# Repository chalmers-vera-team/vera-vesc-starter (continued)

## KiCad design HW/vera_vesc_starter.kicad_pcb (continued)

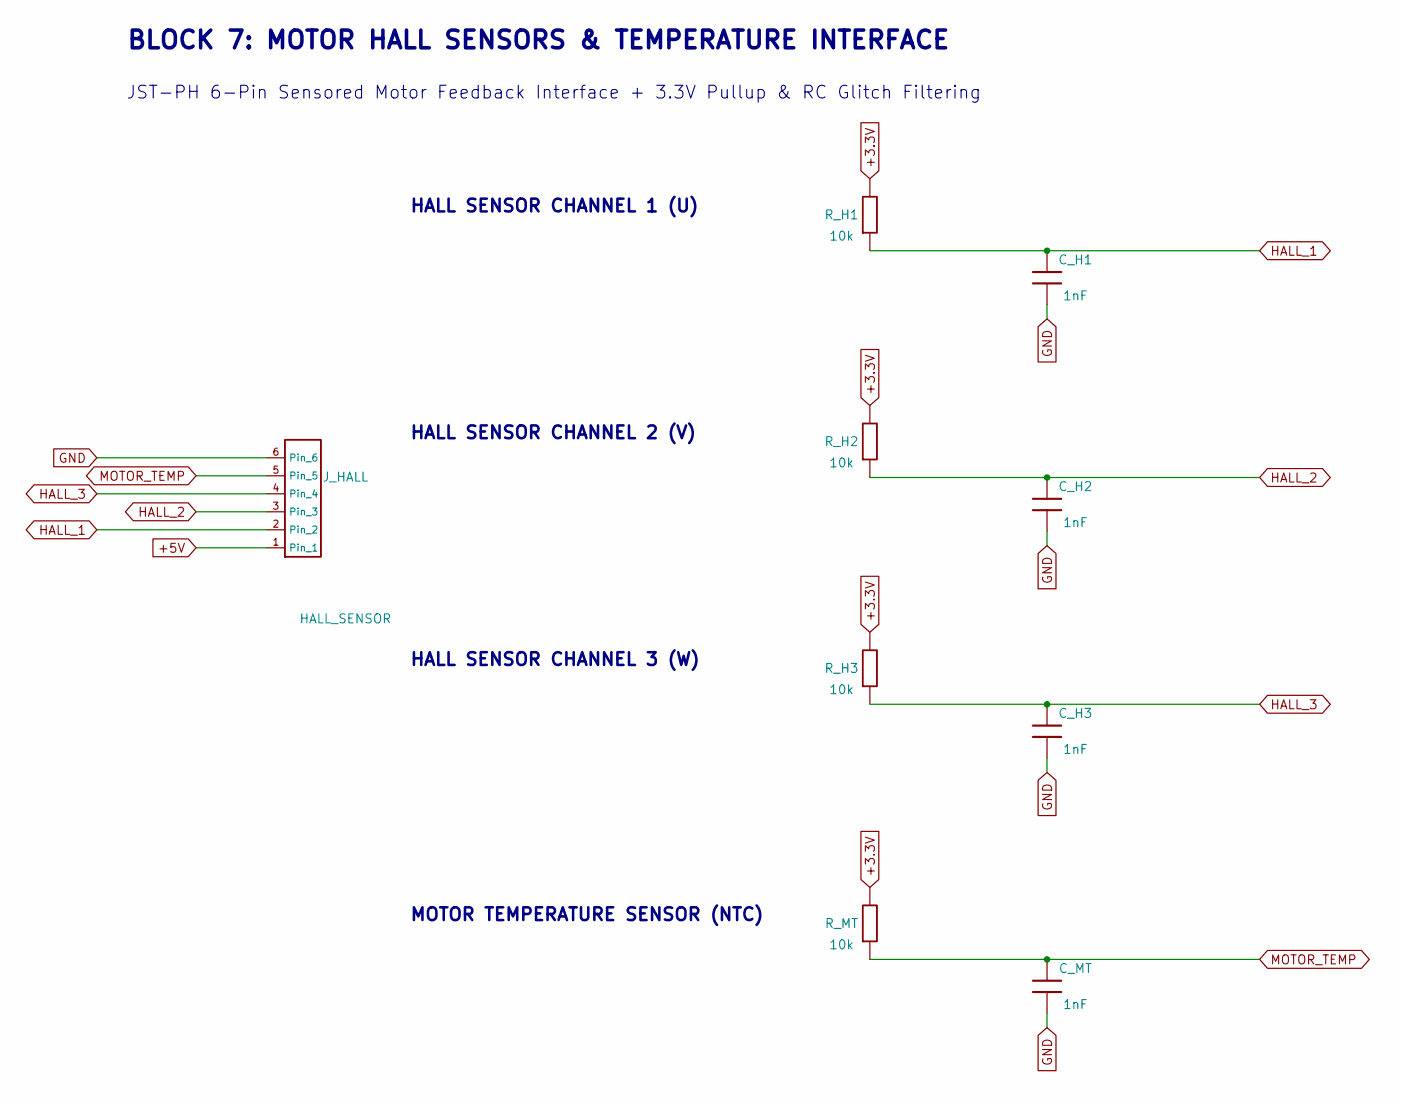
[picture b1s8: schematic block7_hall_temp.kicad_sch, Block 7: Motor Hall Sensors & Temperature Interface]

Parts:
C_H1, C_H2, C_H3: 1nF; C_0603_1608Metric; MPN CC0603KRX7R9BB102
C_MT: 1nF; C_0603_1608Metric; MPN CC0603KRX7R9BB102
J_HALL: HALL_SENSOR; JST_PH_B6B-PH-K_1x06_P2.00mm_Vertical; MPN B6B-PH-K-S
R_H1, R_H2, R_H3: 10k; R_0603_1608Metric; MPN RC0603FR-0710KL
R_MT: 10k; R_0603_1608Metric; MPN RC0603FR-0710KL

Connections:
+3.3V: R_H1.1, R_H2.1, R_H3.1, R_MT.1; also elsewhere on the board
+5V: J_HALL.1; also elsewhere on the board
GND: C_H1.2, C_H2.2, C_H3.2, C_MT.2, J_HALL.6; also elsewhere on the board
HALL_1: C_H1.1, J_HALL.2, R_H1.2; also elsewhere on the board
HALL_2: C_H2.1, J_HALL.3, R_H2.2; also elsewhere on the board
HALL_3: C_H3.1, J_HALL.4, R_H3.2; also elsewhere on the board
MOTOR_TEMP: C_MT.1, J_HALL.5, R_MT.2; also elsewhere on the board

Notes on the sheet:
HALL SENSOR CHANNEL 2 (V)
HALL SENSOR CHANNEL 3 (W)
BLOCK 7: MOTOR HALL SENSORS & TEMPERATURE INTERFACE
HALL SENSOR CHANNEL 1 (U)
MOTOR TEMPERATURE SENSOR (NTC)
JST-PH 6-Pin Sensored Motor Feedback Interface + 3.3V Pullup & RC Glitch Filtering

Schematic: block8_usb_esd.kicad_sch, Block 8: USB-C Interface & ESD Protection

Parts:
C_VBUS: 1uF; C_0603_1608Metric; MPN CC0603KRX7R8BB105
D_VBUS: SMBJ5.0A; D_SMB; MPN SMBJ5.0A-E3/52
J_USB: USB_C_2.0; USB_C_Receptacle_GCT_USB4085; MPN USB4085-GF-A
R_CC1, R_CC2: 5.1k; R_0603_1608Metric; MPN RC0603FR-075K1L
U5: USBLC6-2SC6; SOT-23-6; MPN USBLC6-2SC6

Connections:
GND: C_VBUS.2, D_VBUS.1 (A), J_USB.A1 (GND), J_USB.A12 (GND), J_USB.B1 (GND), J_USB.B12 (GND), J_USB.S1 (SHIELD), J_USB.SH, R_CC1.2, R_CC2.2, U5.2 (GND); also elsewhere on the board
USB_CC1: J_USB.A5 (CC1), R_CC1.1
USB_CC2: J_USB.B5 (CC2), R_CC2.1
USB_DM: U5.4 (IO2); also elsewhere on the board
USB_DM_CON: J_USB.A7 (DN1), J_USB.B7 (DN2), U5.3 (IO2)
USB_DP: U5.6 (IO1); also elsewhere on the board
USB_DP_CON: J_USB.A6 (DP1), J_USB.B6 (DP2), U5.1 (IO1)
VBUS_USB: C_VBUS.1, D_VBUS.2 (K), J_USB.A4 (VBUS), J_USB.A9 (VBUS), J_USB.B4 (VBUS), J_USB.B9 (VBUS), U5.5 (VBUS)

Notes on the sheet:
USB-C Receptacle + 5.1k CC Pulldowns + USBLC6-2SC6 Low-Capacitance TVS Diode Array
AUTOMOTIVE TRANSIENT VOLTAGE SUPPRESSOR
USB-C UFP CONFIGURATION (5.1k PULLDOWNS)
BLOCK 8: USB-C 2.0 INTERFACE & AUTOMOTIVE ESD PROTECTION

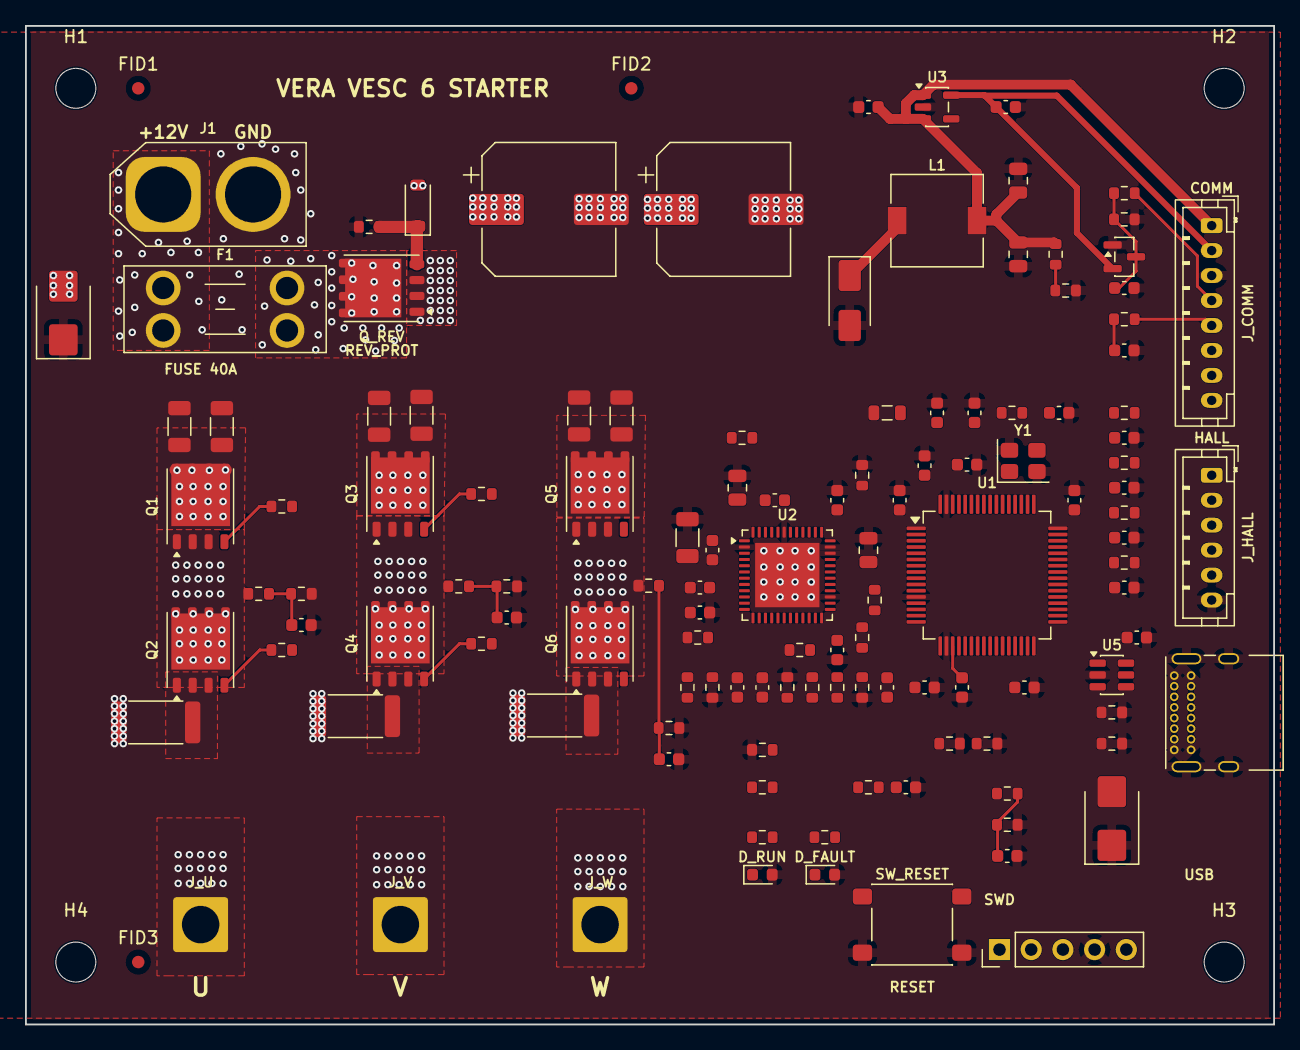
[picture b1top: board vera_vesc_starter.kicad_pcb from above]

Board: 4 copper layers, 100.0 x 80.0 mm, 131 parts (0 on the bottom side), 91 nets.

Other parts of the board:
FID1, FID2, FID3: FIDUCIAL; Fiducial_1mm_Mask2mm
H1, H2, H3, H4: M3; MountingHole_3.2mm_M3
